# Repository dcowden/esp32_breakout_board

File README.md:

# esp32 breakout boards

These are for  this board:

https://docs.espressif.com/projects/esp-dev-kits/en/latest/esp32/_images/esp32_devkitC_v4_pinlayout.png

## Included boards
 1. **esp32_breakout_smt**  A board designed to expose the stuff i need for xcc tracker, all on one board, with smt style mounts
 2. **esp32_breakout_tht** Through hole version of the above ( again designed for the xc case in mind
 3. **esp32_breakout_tht2** A simple board designed to just break out pins-- and then extned through a shield approach
 4. **esp32_breakout_tht2_shield** A shield for the agove that adds the stuff needed for xc application
 
## The stuff that the XC board needs

The xc board logs data from an nrf52840 and sends it to an esp32 , which processes further. 
The board needs:
   1. esp32 devkit c ( we need all the pins) (38 pin)
   2. seed xiao nrf52840  (14 pin) 
   3. ds3231 (isc) (weird 5 pin thing)
   4. i2c oled 
   5. micro sd card holder ( spi )

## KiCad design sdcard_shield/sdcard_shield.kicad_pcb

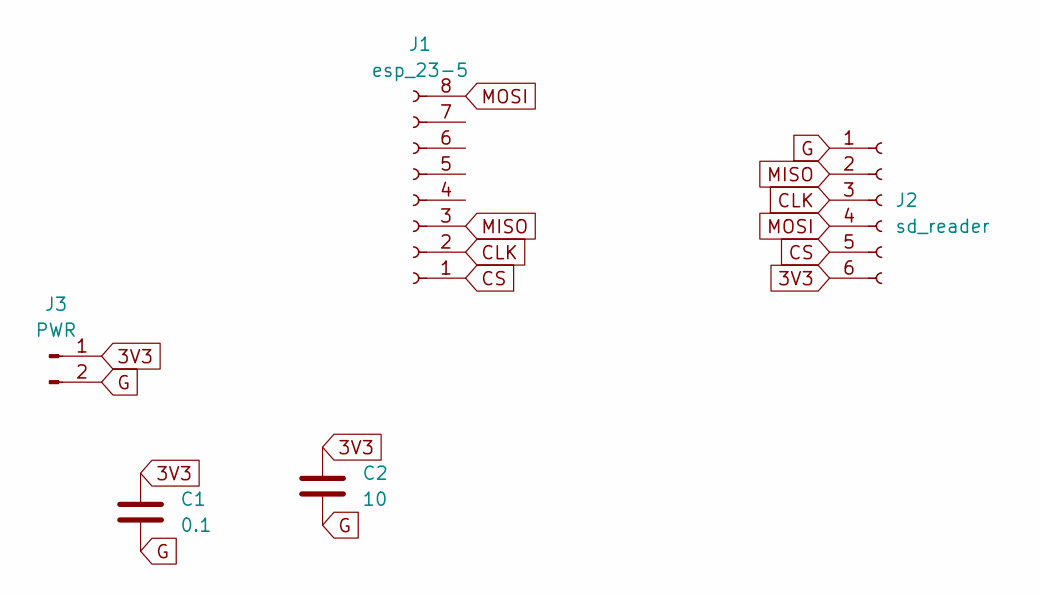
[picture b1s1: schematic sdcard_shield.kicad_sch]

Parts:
C1: 0.1; CP_Radial_D5.0mm_P2.50mm
C2: 10; CP_Radial_D5.0mm_P2.50mm
J1: esp_23-5; PinHeader_1x08_P2.54mm_Vertical
J2: sd_reader; PinHeader_1x06_P2.54mm_Vertical
J3: PWR; PinHeader_1x02_P2.54mm_Vertical

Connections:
3V3: C1.1, C2.1, J2.6, J3.1
CLK: J1.2, J2.3
CS: J1.1, J2.5
G: C1.2, C2.2, J2.1, J3.2
MISO: J1.3, J2.2
MOSI: J1.8, J2.4

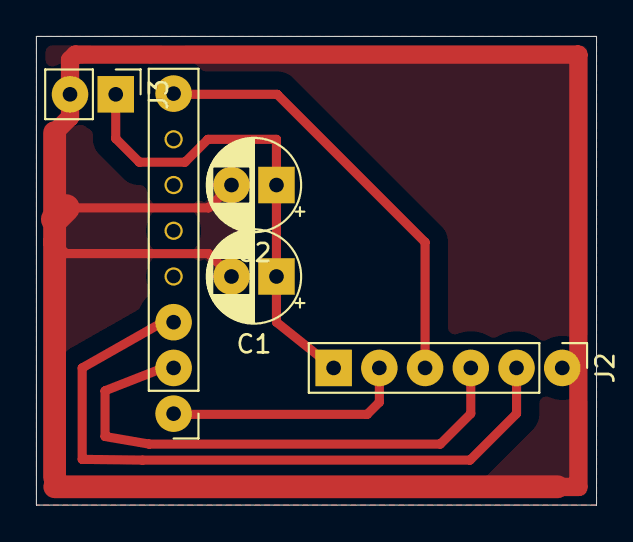
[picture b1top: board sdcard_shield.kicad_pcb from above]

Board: 2 copper layers, 31.1 x 26.0 mm, 5 parts (0 on the bottom side), 6 nets.

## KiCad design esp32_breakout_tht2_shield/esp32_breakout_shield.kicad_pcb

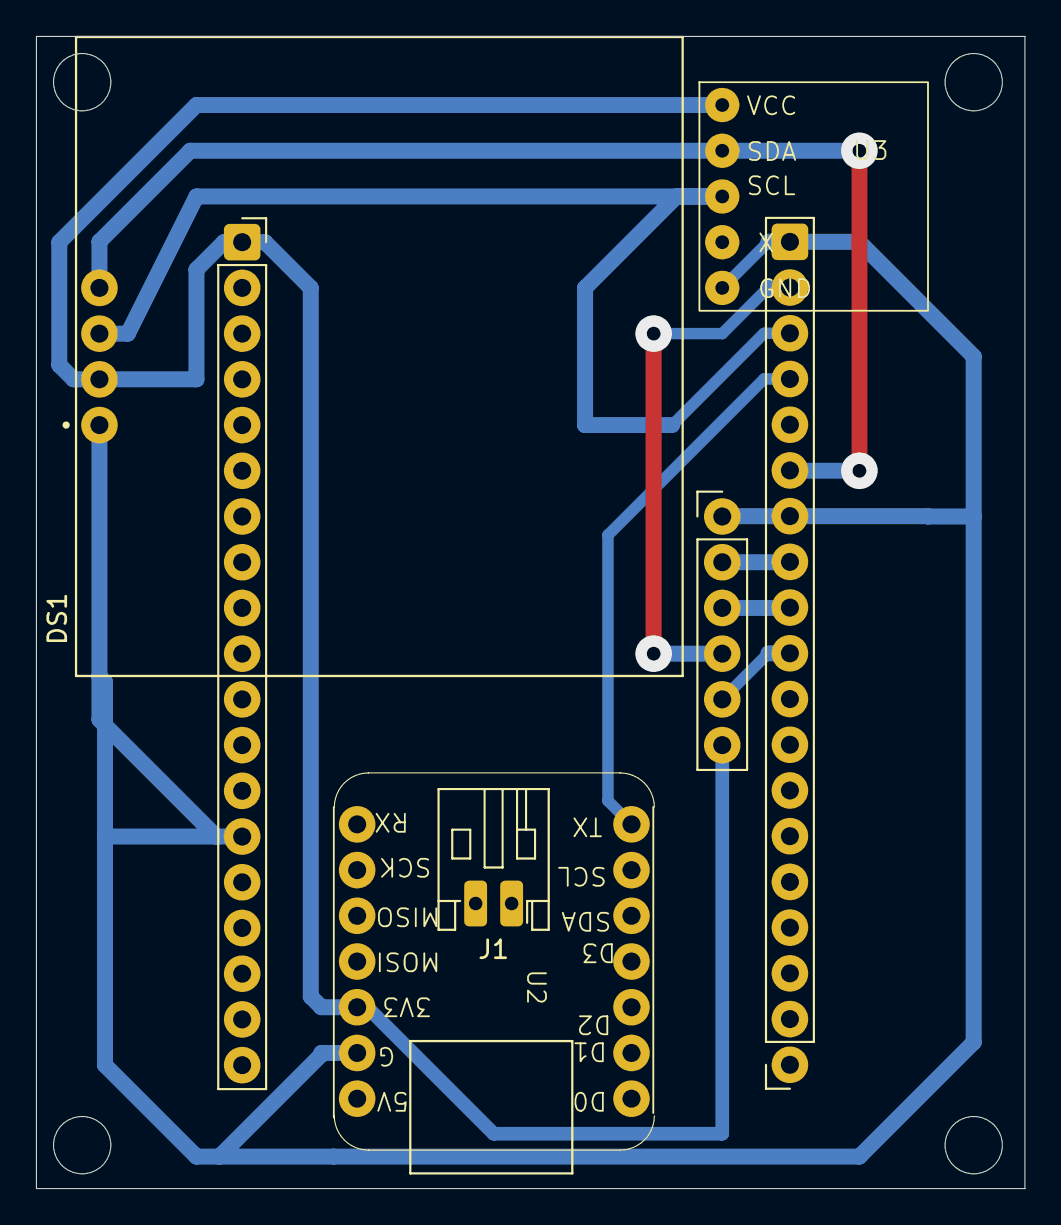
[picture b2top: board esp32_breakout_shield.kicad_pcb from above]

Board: 2 copper layers, 54.9 x 64.0 mm, 7 parts (0 on the bottom side), 12 nets.

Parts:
DS1: OLED_128X64_1.3_I2C; LCD_OLED_128X64_1.3_I2C
J1: BAT; JST_PH_S2B-PH-K_1x02_P2.00mm_Horizontal
J21: SPI1; PinHeader_1x06_P2.54mm_Vertical
J23: s2; PinSocket_1x19_P2.54mm_Vertical_Tight
J24: s1; PinSocket_1x19_P2.54mm_Vertical_Tight
U2: XIAO_NRF52840
U3: DS3231

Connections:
3V3: DS1.2 (VDD), J21.6, J23.1, U2.5 (3V3), U3.1 (VCC)
GND: DS1.1 (GND), J21.1, J23.14, J24.13, J24.19, U2.6 (GND), U3.5 (GND)
I2C_SCL: DS1.3 (SCK), J24.17, U3.3 (SCL)
I2C_SDA: DS1.4 (SDA), J24.14, U3.2 (SDA)
unnamed: J1.1, U2.16 (BAT-)
unnamed: J1.2, U2.15 (BAT+)
SPI_CS: J21.5, J24.10
SPI_MISO: J21.2, J24.12
SPI_MOSI: J21.4, J24.18
SPI_SCK: J21.3, J24.11
U0_RX: J24.16, U2.8 (TX)
U0_TX: J24.15, U2.1 (RX)

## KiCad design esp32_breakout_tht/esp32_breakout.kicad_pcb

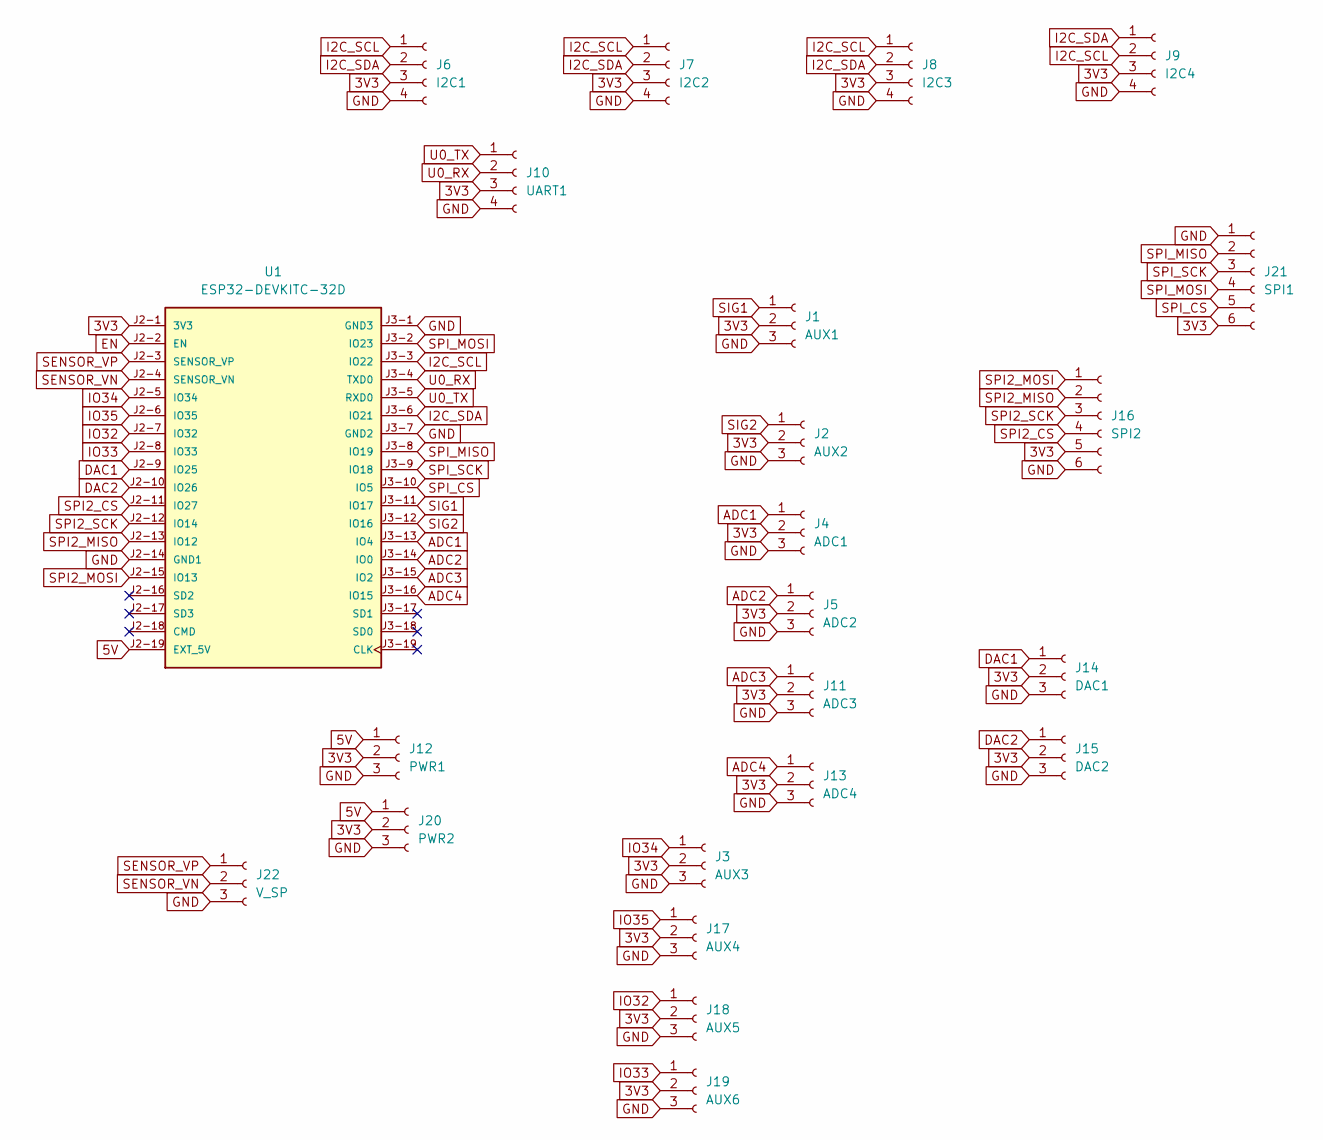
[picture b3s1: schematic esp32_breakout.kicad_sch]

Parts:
J1: AUX1; PinHeader_1x03_P2.54mm_Vertical
J2: AUX2; PinHeader_1x03_P2.54mm_Vertical
J3: AUX3; PinHeader_1x03_P2.54mm_Vertical
J4: ADC1; PinHeader_1x03_P2.54mm_Vertical
J5: ADC2; PinHeader_1x03_P2.54mm_Vertical
J6: I2C1; PinHeader_1x04_P2.54mm_Vertical
J7: I2C2; PinHeader_1x04_P2.54mm_Vertical
J8: I2C3; PinHeader_1x04_P2.54mm_Vertical
J9: I2C4; PinHeader_1x04_P2.54mm_Vertical
J10: UART1; PinHeader_1x04_P2.54mm_Vertical
J11: ADC3; PinHeader_1x03_P2.54mm_Vertical
J12: PWR1; PinHeader_1x03_P2.54mm_Vertical
J13: ADC4; PinHeader_1x03_P2.54mm_Vertical
J14: DAC1; PinHeader_1x03_P2.54mm_Vertical
J15: DAC2; PinHeader_1x03_P2.54mm_Vertical
J16: SPI2; PinHeader_1x06_P2.54mm_Vertical
J17: AUX4; PinHeader_1x03_P2.54mm_Vertical
J18: AUX5; PinHeader_1x03_P2.54mm_Vertical
J19: AUX6; PinHeader_1x03_P2.54mm_Vertical
J20: PWR2; PinHeader_1x03_P2.54mm_Vertical
J21: SPI1; PinHeader_1x06_P2.54mm_Vertical
J22: V_SP; PinHeader_1x03_P2.54mm_Vertical
U1: ESP32-DEVKITC-32D; MODULE_ESP32-DEVKITC-32D-THT; PARTREV V4

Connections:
3V3: J1.2, J2.2, J3.2, J4.2, J5.2, J6.3, J7.3, J8.3, J9.3, J10.3, J11.2, J12.2, J13.2, J14.2, J15.2, J16.5, J17.2, J18.2, J19.2, J20.2, J21.6, U1.J2-1 (3V3)
5V: J12.1, J20.1, U1.J2-19 (EXT_5V)
ADC1: J4.1, U1.J3-13 (IO4)
ADC2: J5.1, U1.J3-14 (IO0)
ADC3: J11.1, U1.J3-15 (IO2)
ADC4: J13.1, U1.J3-16 (IO15)
DAC1: J14.1, U1.J2-9 (IO25)
DAC2: J15.1, U1.J2-10 (IO26)
EN: U1.J2-2 (EN)
GND: J1.3, J2.3, J3.3, J4.3, J5.3, J6.4, J7.4, J8.4, J9.4, J10.4, J11.3, J12.3, J13.3, J14.3, J15.3, J16.6, J17.3, J18.3, J19.3, J20.3, J21.1, J22.3, U1.J2-14 (GND1), U1.J3-1 (GND3), U1.J3-7 (GND2)
I2C_SCL: J6.1, J7.1, J8.1, J9.2, U1.J3-3 (IO22)
I2C_SDA: J6.2, J7.2, J8.2, J9.1, U1.J3-6 (IO21)
IO32: J18.1, U1.J2-7 (IO32)
IO33: J19.1, U1.J2-8 (IO33)
IO34: J3.1, U1.J2-5 (IO34)
IO35: J17.1, U1.J2-6 (IO35)
SENSOR_VN: J22.2, U1.J2-4 (SENSOR_VN)
SENSOR_VP: J22.1, U1.J2-3 (SENSOR_VP)
SIG1: J1.1, U1.J3-11 (IO17)
SIG2: J2.1, U1.J3-12 (IO16)
SPI2_CS: J16.4, U1.J2-11 (IO27)
SPI2_MISO: J16.2, U1.J2-13 (IO12)
SPI2_MOSI: J16.1, U1.J2-15 (IO13)
SPI2_SCK: J16.3, U1.J2-12 (IO14)
SPI_CS: J21.5, U1.J3-10 (IO5)
SPI_MISO: J21.2, U1.J3-8 (IO19)
SPI_MOSI: J21.4, U1.J3-2 (IO23)
SPI_SCK: J21.3, U1.J3-9 (IO18)
U0_RX: J10.2, U1.J3-4 (TXD0)
U0_TX: J10.1, U1.J3-5 (RXD0)

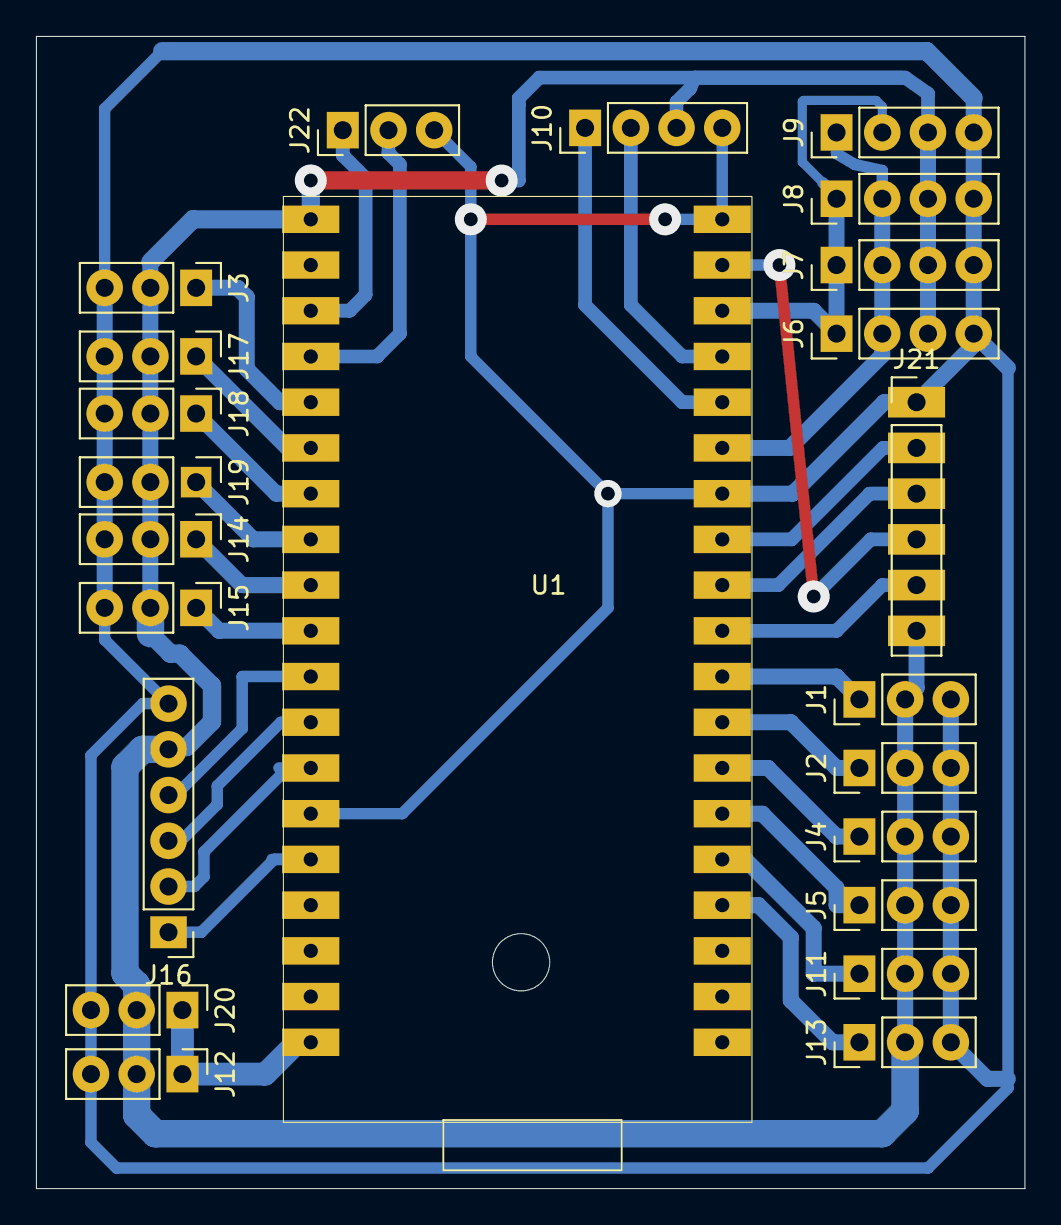
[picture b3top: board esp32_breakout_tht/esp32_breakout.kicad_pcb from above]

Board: 2 copper layers, 54.9 x 64.0 mm, 23 parts (0 on the bottom side), 29 nets.

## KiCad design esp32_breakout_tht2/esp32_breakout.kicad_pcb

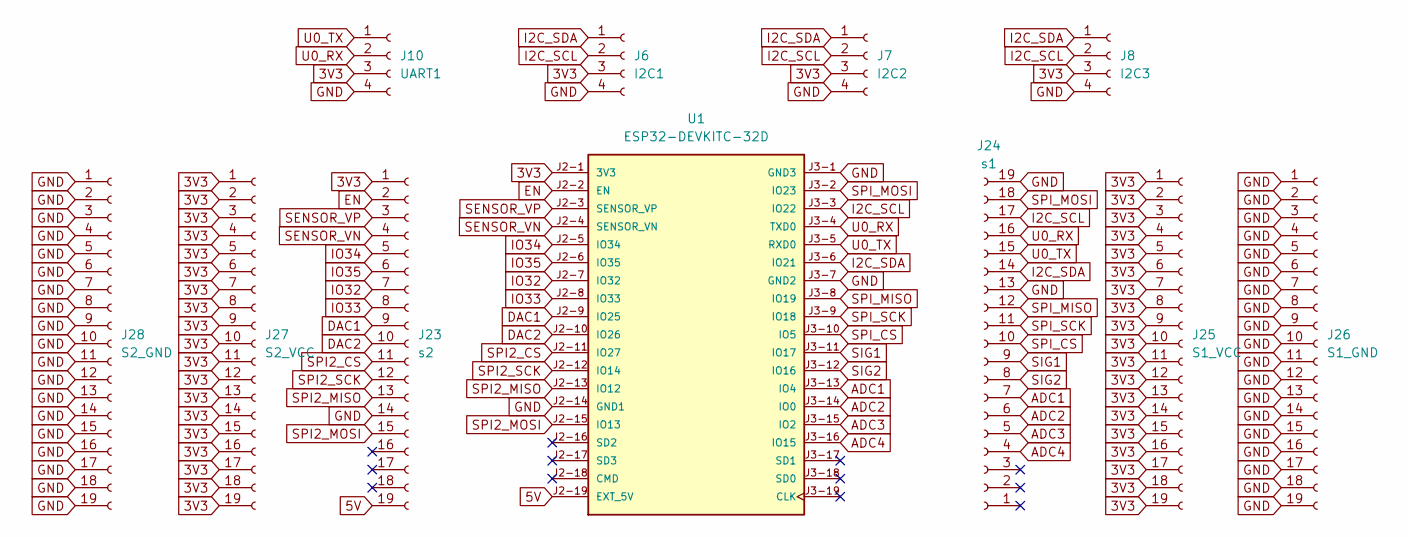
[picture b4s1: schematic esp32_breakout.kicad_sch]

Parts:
J6: I2C1; PinHeader_1x04_P2.54mm_Vertical_tight
J7: I2C2; PinHeader_1x04_P2.54mm_Vertical_tight
J8: I2C3; PinHeader_1x04_P2.54mm_Vertical_tight
J10: UART1; PinHeader_1x04_P2.54mm_Vertical_tight
J23: s2; PinSocket_1x19_P2.54mm_Vertical_Tight
J24: s1; PinSocket_1x19_P2.54mm_Vertical_Tight
J25: S1_VCC; PinSocket_1x19_P2.54mm_Vertical_Tight
J26: S1_GND; PinSocket_1x19_P2.54mm_Vertical_Tight
J27: S2_VCC; PinSocket_1x19_P2.54mm_Vertical_Tight
J28: S2_GND; PinSocket_1x19_P2.54mm_Vertical_Tight
U1: ESP32-DEVKITC-32D; MODULE_ESP32-DEVKITC-32D-THT; PARTREV V4

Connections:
3V3: J6.3, J7.3, J8.3, J10.3, J23.1, J25.1, J25.2, J25.3, J25.4, J25.5, J25.6, J25.7, J25.8, J25.9, J25.10, J25.11, J25.12, J25.13, J25.14, J25.15, J25.16, J25.17, J25.18, J25.19, J27.1, J27.2, J27.3, J27.4, J27.5, J27.6, J27.7, J27.8, J27.9, J27.10, J27.11, J27.12, J27.13, J27.14, J27.15, J27.16, J27.17, J27.18, J27.19, U1.J2-1 (3V3)
5V: J23.19, U1.J2-19 (EXT_5V)
ADC1: J24.7, U1.J3-13 (IO4)
ADC2: J24.6, U1.J3-14 (IO0)
ADC3: J24.5, U1.J3-15 (IO2)
ADC4: J24.4, U1.J3-16 (IO15)
DAC1: J23.9, U1.J2-9 (IO25)
DAC2: J23.10, U1.J2-10 (IO26)
EN: J23.2, U1.J2-2 (EN)
GND: J6.4, J7.4, J8.4, J10.4, J23.14, J24.13, J24.19, J26.1, J26.2, J26.3, J26.4, J26.5, J26.6, J26.7, J26.8, J26.9, J26.10, J26.11, J26.12, J26.13, J26.14, J26.15, J26.16, J26.17, J26.18, J26.19, J28.1, J28.2, J28.3, J28.4, J28.5, J28.6, J28.7, J28.8, J28.9, J28.10, J28.11, J28.12, J28.13, J28.14, J28.15, J28.16, J28.17, J28.18, J28.19, U1.J2-14 (GND1), U1.J3-1 (GND3), U1.J3-7 (GND2)
I2C_SCL: J6.2, J7.2, J8.2, J24.17, U1.J3-3 (IO22)
I2C_SDA: J6.1, J7.1, J8.1, J24.14, U1.J3-6 (IO21)
IO32: J23.7, U1.J2-7 (IO32)
IO33: J23.8, U1.J2-8 (IO33)
IO34: J23.5, U1.J2-5 (IO34)
IO35: J23.6, U1.J2-6 (IO35)
SENSOR_VN: J23.4, U1.J2-4 (SENSOR_VN)
SENSOR_VP: J23.3, U1.J2-3 (SENSOR_VP)
SIG1: J24.9, U1.J3-11 (IO17)
SIG2: J24.8, U1.J3-12 (IO16)
SPI2_CS: J23.11, U1.J2-11 (IO27)
SPI2_MISO: J23.13, U1.J2-13 (IO12)
SPI2_MOSI: J23.15, U1.J2-15 (IO13)
SPI2_SCK: J23.12, U1.J2-12 (IO14)
SPI_CS: J24.10, U1.J3-10 (IO5)
SPI_MISO: J24.12, U1.J3-8 (IO19)
SPI_MOSI: J24.18, U1.J3-2 (IO23)
SPI_SCK: J24.11, U1.J3-9 (IO18)
U0_RX: J10.2, J24.16, U1.J3-4 (TXD0)
U0_TX: J10.1, J24.15, U1.J3-5 (RXD0)

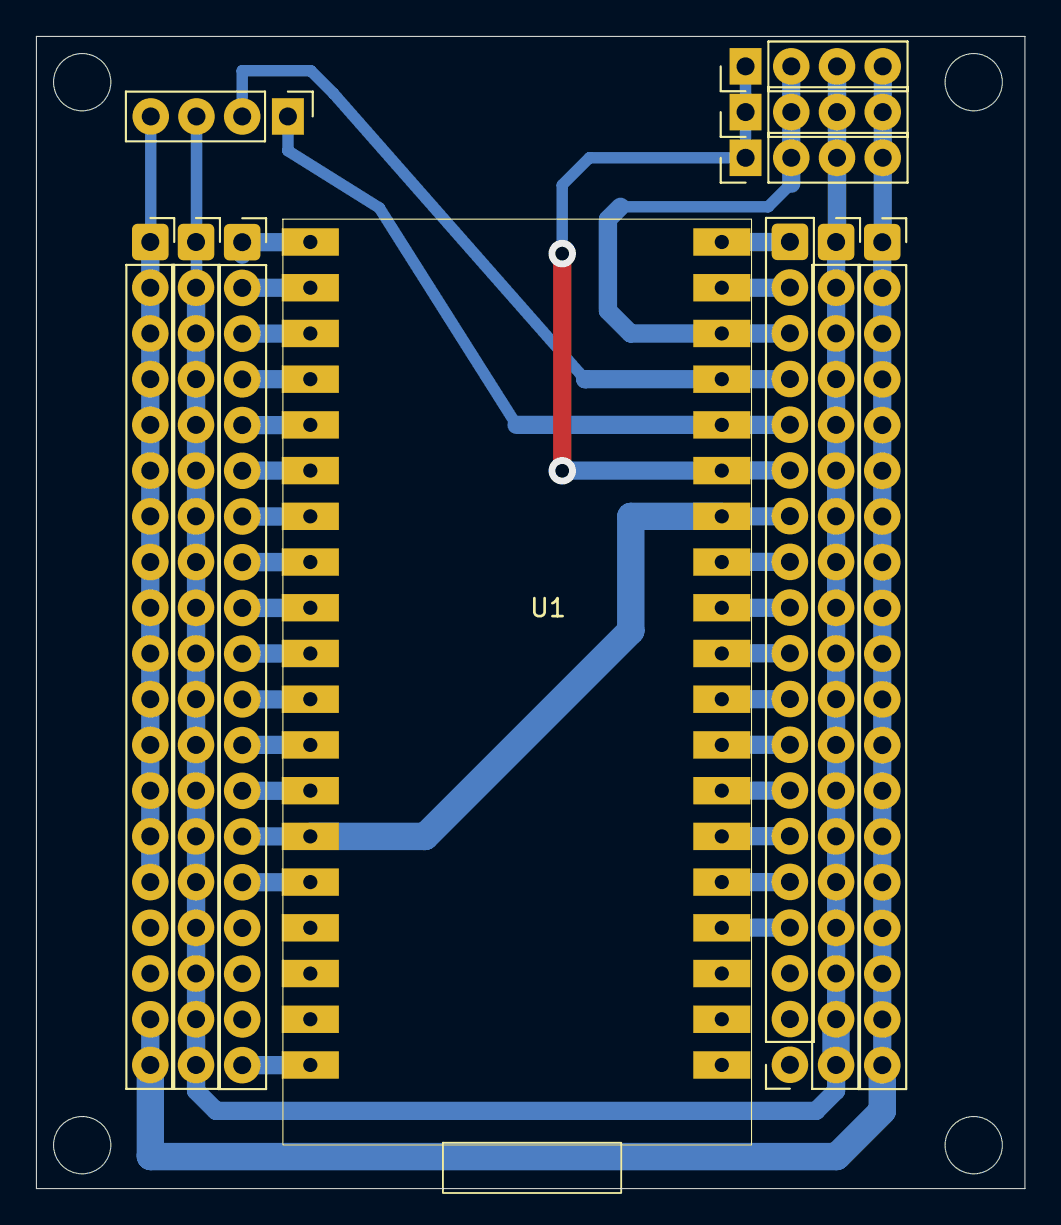
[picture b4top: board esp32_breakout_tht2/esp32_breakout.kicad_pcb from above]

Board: 2 copper layers, 54.9 x 64.0 mm, 11 parts (0 on the bottom side), 30 nets.

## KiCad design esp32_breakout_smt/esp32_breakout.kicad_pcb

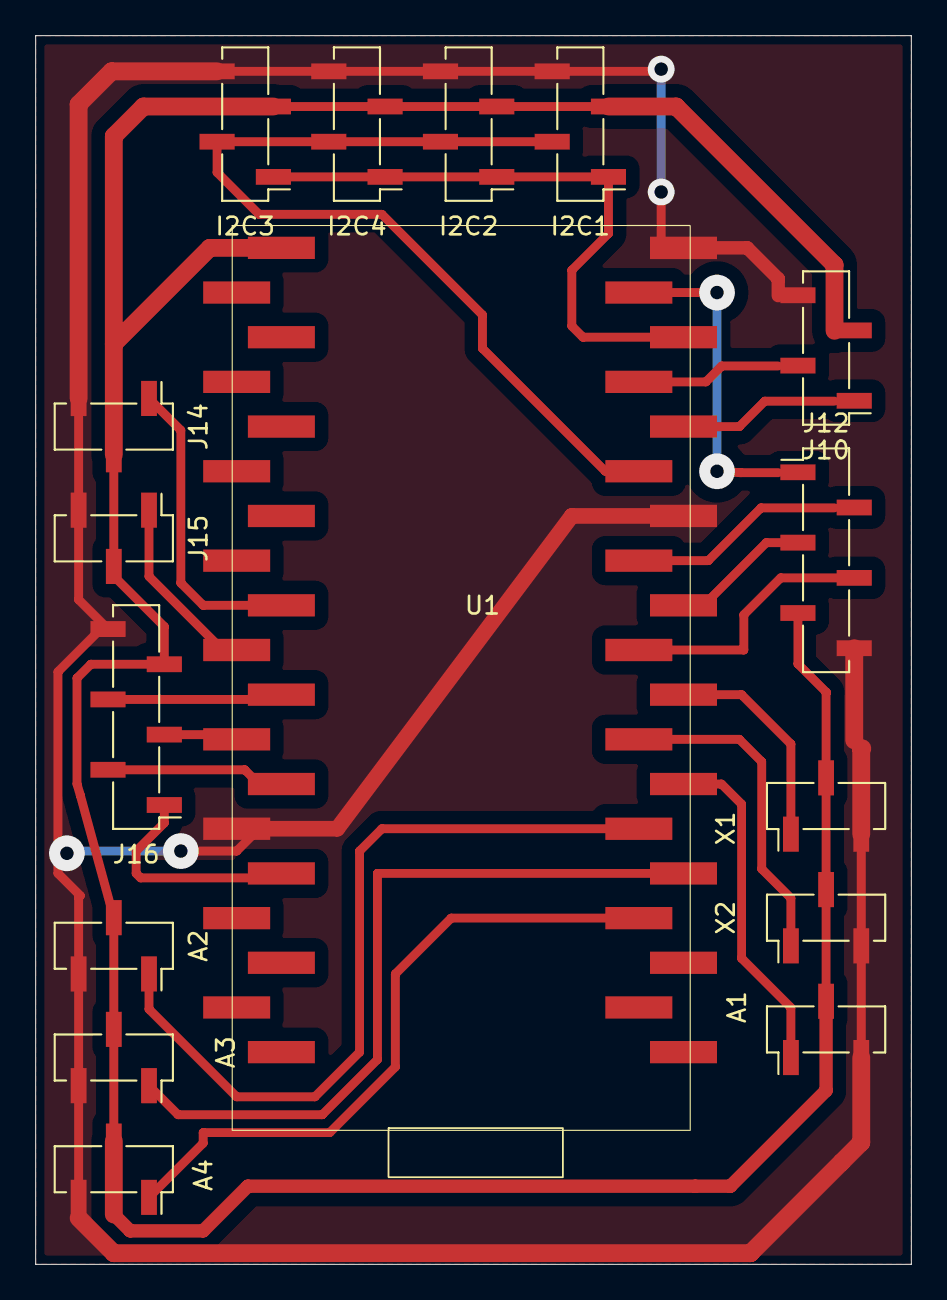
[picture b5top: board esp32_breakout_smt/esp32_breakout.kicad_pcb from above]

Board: 2 copper layers, 49.8 x 69.8 mm, 16 parts (0 on the bottom side), 22 nets.

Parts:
A1: ADC1; PinSocket_1x03_P2.00mm_Vertical_SMD_Pin1Left
A2: ADC2; PinSocket_1x03_P2.00mm_Vertical_SMD_Pin1Right
A3: ADC3; PinSocket_1x03_P2.00mm_Vertical_SMD_Pin1Right
A4: ADC4; PinSocket_1x03_P2.00mm_Vertical_SMD_Pin1Right
I2C1: I2C1; PinSocket_1x04_P2.00mm_Vertical_SMD_Pin1Left
I2C2: I2C2; PinSocket_1x04_P2.00mm_Vertical_SMD_Pin1Left
I2C3: I2C4; PinSocket_1x04_P2.00mm_Vertical_SMD_Pin1Left
I2C4: I2C3; PinSocket_1x04_P2.00mm_Vertical_SMD_Pin1Left
J10: UART1; PinSocket_1x04_P2.00mm_Vertical_SMD_Pin1Left
J12: SPI1; PinSocket_1x06_P2.00mm_Vertical_SMD_Pin1Left
J14: DAC1; PinSocket_1x03_P2.00mm_Vertical_SMD_Pin1Left
J15: DAC2; PinSocket_1x03_P2.00mm_Vertical_SMD_Pin1Left
J16: SPI2; PinSocket_1x06_P2.00mm_Vertical_SMD_Pin1Left
U1: ESP32-DEVKITC-32D; MODULE_ESP32-DEVKITC-32D
X1: AUX1; PinSocket_1x03_P2.00mm_Vertical_SMD_Pin1Left
X2: AUX2; PinSocket_1x03_P2.00mm_Vertical_SMD_Pin1Left

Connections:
3V3: A1.2, A2.2, A3.2, A4.2, I2C1.3, I2C2.3, I2C3.3, I2C4.3, J10.3, J12.5, J14.2, J15.2, J16.5, U1.J2-1 (3V3), X1.2, X2.2
ADC1: A1.1, U1.J3-13 (IO4)
ADC2: A2.1, U1.J3-14 (IO0)
ADC3: A3.1, U1.J3-15 (IO2)
ADC4: A4.1, U1.J3-16 (IO15)
DAC1: J14.1, U1.J2-9 (IO25)
DAC2: J15.1, U1.J2-10 (IO26)
GND: A1.3, A2.3, A3.3, A4.3, I2C1.4, I2C2.4, I2C3.4, I2C4.4, J10.4, J12.6, J14.3, J15.3, J16.6, U1.J2-14 (GND1), U1.J3-1 (GND3), U1.J3-7 (GND2), X1.3, X2.3
I2C_SCL: I2C1.1, I2C2.1, I2C3.1, I2C4.1, U1.J3-3 (IO22)
I2C_SDA: I2C1.2, I2C2.2, I2C3.2, I2C4.2, U1.J3-6 (IO21)
SIG1: U1.J3-11 (IO17), X1.1
SIG2: U1.J3-12 (IO16), X2.1
SPI2_CS: J16.4, U1.J2-11 (IO27)
SPI2_MISO: J16.2, U1.J2-13 (IO12)
SPI2_MOSI: J16.1, U1.J2-15 (IO13)
SPI2_SCK: J16.3, U1.J2-12 (IO14)
SPI_CS: J12.4, U1.J3-10 (IO5)
SPI_MISO: J12.2, U1.J3-8 (IO19)
SPI_MOSI: J12.1, U1.J3-2 (IO23)
SPI_SCK: J12.3, U1.J3-9 (IO18)
U0_RX: J10.2, U1.J3-4 (TXD0)
U0_TX: J10.1, U1.J3-5 (RXD0)

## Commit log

2025-12-13 first version
2025-12-13 little bigger board
2025-12-13 handled kerf
2025-12-14 now the kerf adjust is actually working
2025-12-14 made shield style boards
2025-12-14 describe what all these boards are
2025-12-14 generated all the boards, touched up
2025-12-14 added fab alignment box
2025-12-20 added sdcard shield to clean up reliability
2025-12-20 fixed it
2025-12-20 dammit. fixed
